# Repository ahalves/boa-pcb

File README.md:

# boa-pcb
(b)lackjack (o)n (a) pcb
-----
<sup><sub>ignore the kicad files' names they were too annoying to change</sub></sup>

### howto
long flash = 5
short flash = 1

leds work as following left to right:
- your score: as above
- dealer's score: as above
- turn indicator: on when it's your turn
- win/loss indicator: fast flashing, you win; slow flashing, you drew; stays on: you lost

buttons work as following left to right:
- deal
- hit
- stand
- reset - at the end of the game

## le devlog

### Session 1 - 14 November 2025 - 20 minutes

Completed the schematic.

### Session 1 - 14 November 2025 - 30 minutes

Made the PCB look nice, though I haven't routed traces yet :pf:

### Session 1 - 14 November 2025 - 10 minutes

Routed traces

### Session 1 - 14 November 2025 - 5 minutes

Added fills and tidied up footprints (_aesthetics_ ✨)

### Session 1 - 14 November 2025 - 10 minutes

I realised its probably better to have the MCU pointing up, so I rearranged and rerouted it.

### Session 1 - 14 November 2025 - 30 minutes

Did some coding, yet to implement the keypresses.

### Session 1 - 14 November 2025 - 40 minutes

Finished the code!

### Session 2 - 23 November 2025 - 30 minutes

big refactor - now it's a blackjack game... need to code

### Session 3 - 26 November 2025 - 45 minutes

finished the code!

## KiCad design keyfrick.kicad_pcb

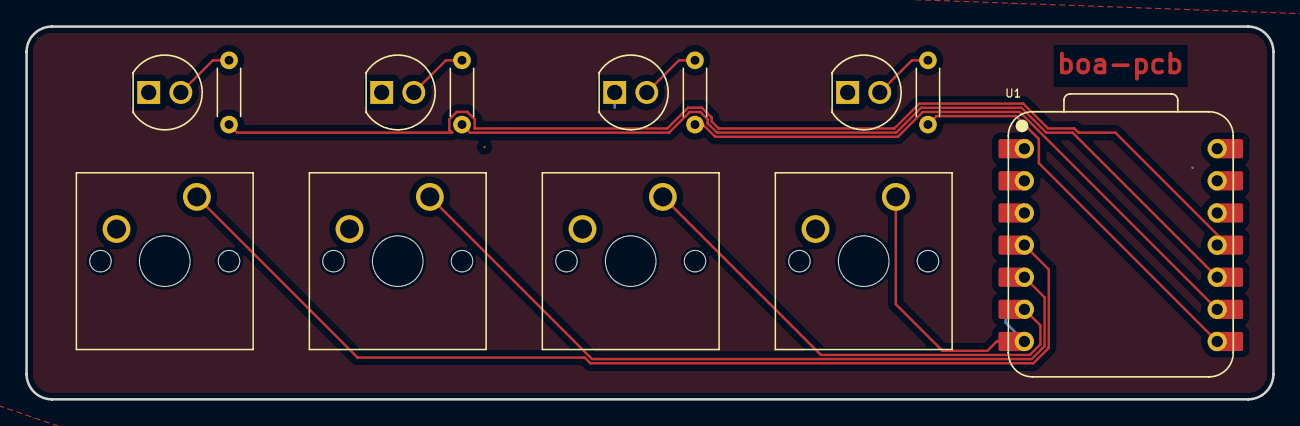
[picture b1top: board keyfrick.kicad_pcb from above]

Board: 2 copper layers, 98.6 x 29.5 mm, 13 parts (0 on the bottom side), 13 nets.

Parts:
D1, D2, D3, D4: L08R5000Q1; LEDRD254W57D500H1070
R1, R2, R3, R4: R; R_Axial_DIN0204_L3.6mm_D1.6mm_P5.08mm_Horizontal
SW1, SW2, SW3, SW4: SW_Push; SW_Cherry_MX_1.00u_PCB
U1: XIAO-RP2040-DIP

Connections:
GND: D1.C, D2.C, D3.C, D4.C, SW1.2, SW2.2, SW3.2, SW4.2, U1.13 (GND)
unnamed: D1.A, R1.1
unnamed: D2.A, R2.1
unnamed: D3.A, R3.1
unnamed: D4.A, R4.1
d1: R1.2, U1.11 (GPIO3/MOSI)
d2: R2.2, U1.10 (GPIO4/MISO)
d3: R3.2, U1.9 (GPIO2/SCK)
d4: R4.2, U1.8 (GPIO1/RX)
sw1: SW1.1, U1.4 (GPIO29/ADC3/A3)
sw2: SW2.1, U1.5 (GPIO6/SDA)
sw3: SW3.1, U1.6 (GPIO7/SCL)
sw4: SW4.1, U1.7 (GPIO0/TX)

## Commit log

2025-11-14 Rename LEDRD254W57D500H1070.kicad_mod to footprints/LEDRD254W57D500H1070.kicad_mod
2025-11-14 Rename L08R5000Q1.kicad_sym to symbols/L08R5000Q1.kicad_sym
2025-11-14 spent way too long on making the board look good
2025-11-14 routed pcb traces
2025-11-15 final upload
